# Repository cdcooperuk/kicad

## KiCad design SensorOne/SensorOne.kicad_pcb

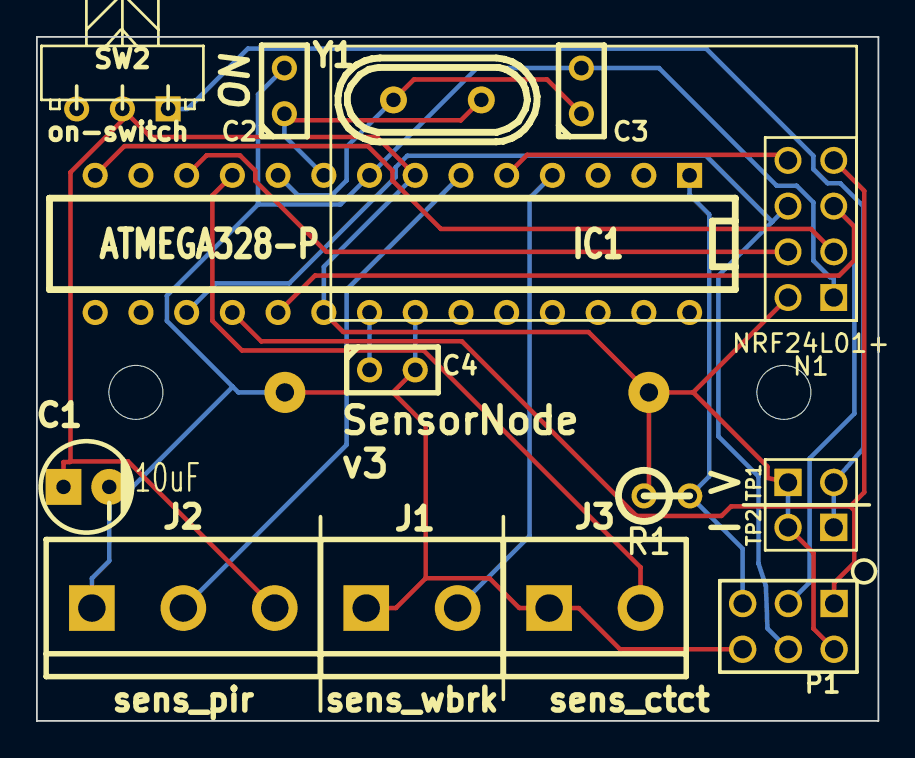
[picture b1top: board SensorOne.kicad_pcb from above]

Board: 2 copper layers, 46.8 x 38.0 mm, 18 parts (1 on the bottom side), 16 nets.

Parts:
BT1: BATTERY; CR2032H
C1: 10uF; CP_5x11mm
C2, C3: 22pF; C1
C4: 100nF; C1
IC1: ATMEGA328-P; DIP-28__300
J1: sens_wbrk; bornier2
J2: sens_pir; bornier3
J3: sens_ctct; bornier2
MH1, MH2: MOUNTING_HOLE_PLACEHOLDER; MountingHole_3mm_RevA_Date21Jun2010
N1: NRF24L01+; cdc_nrf24l01p
P1: icsp; pin_array_3x2
R1: 10k; R1
SW2: on-switch; MINSLIDE_SPDT
TP1: V test; PIN_ARRAY_2X1
TP2: I test; PIN_ARRAY_2X1
Y1: 8MHz; Crystal_HC49-U_Vertical_RevA_09Aug2010

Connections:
+3.3V: BT1.1, C1.1, IC1.7, IC1.20, J2.3, N1.2, P1.2, R1.1, SW2.2, TP1.1, TP2.2
GND: BT1.2, C1.2, C2.2, C3.2, C4.2, IC1.8, IC1.22, J1.1, J2.1, J3.1, N1.1, P1.6
unnamed: C2.1, IC1.9, Y1.2
unnamed: C3.1, IC1.10, Y1.1
unnamed: C4.1, IC1.21
unnamed: IC1.1, P1.5, R1.2
unnamed: IC1.4, J1.2
unnamed: IC1.5, N1.8
unnamed: IC1.6, J2.2
unnamed: IC1.11, J3.2
unnamed: IC1.12, N1.4
unnamed: IC1.14, N1.3
unnamed: IC1.17, N1.6, P1.4
unnamed: IC1.18, N1.7, P1.1
unnamed: IC1.19, N1.5, P1.3
unnamed: SW2.1, TP1.2, TP2.1

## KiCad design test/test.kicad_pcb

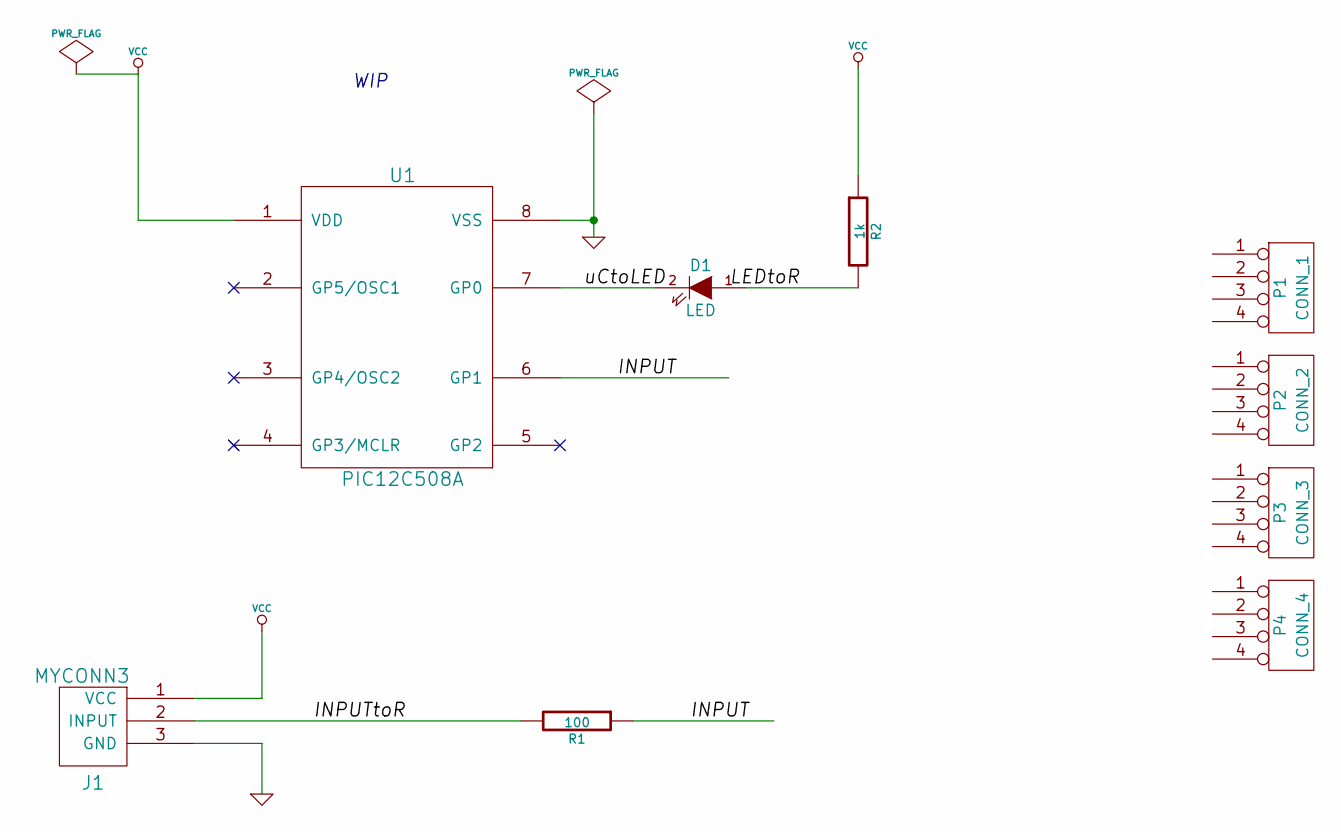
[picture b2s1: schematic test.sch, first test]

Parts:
D1: LED
J1: MYCONN3
P1: CONN_1
P2: CONN_2
P3: CONN_3
P4: CONN_4
R1: 100
R2: 1k
U1: PIC12C508A

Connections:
/INPUT: R1.1, U1.6 (GP1)
/INPUTtoR: J1.2 (INPUT), R1.2
/a1: P1.1, P2.1, P3.1, P4.1
/a2: P1.2, P2.2, P3.2, P4.2
/a3: P1.3, P2.3, P3.3, P4.3
/a4: P1.4, P2.4, P3.4, P4.4
/uCtoLED: D1.2 (K), U1.7 (GP0)
GND: J1.3 (GND), U1.8 (VSS)
unnamed: D1.1 (A), R2.2
VCC: J1.1 (VCC), R2.1, U1.1 (VDD)

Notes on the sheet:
WIP

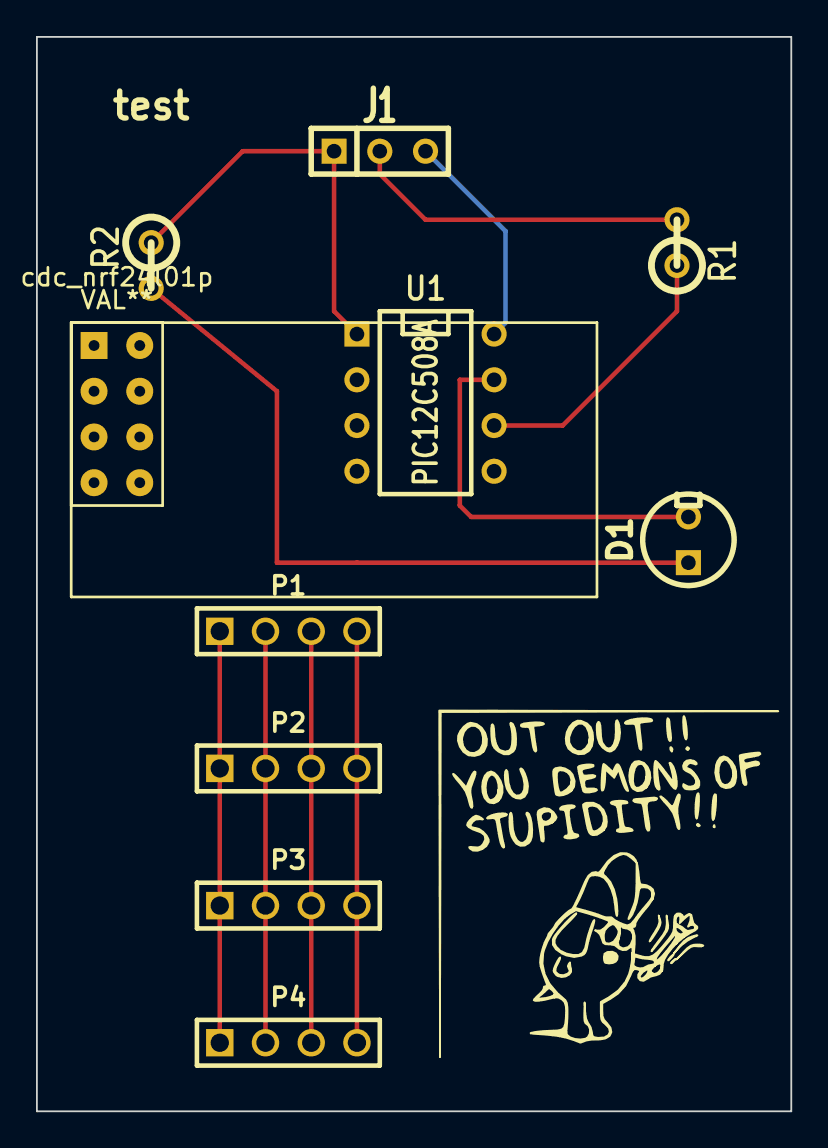
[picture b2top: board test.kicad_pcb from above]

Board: 2 copper layers, 41.9 x 59.7 mm, 10 parts (0 on the bottom side), 10 nets.

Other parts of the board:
cdc_nrf24l01p: VAL**; cdc_nrf24l01p

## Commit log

2013-12-05 initial commit comment
